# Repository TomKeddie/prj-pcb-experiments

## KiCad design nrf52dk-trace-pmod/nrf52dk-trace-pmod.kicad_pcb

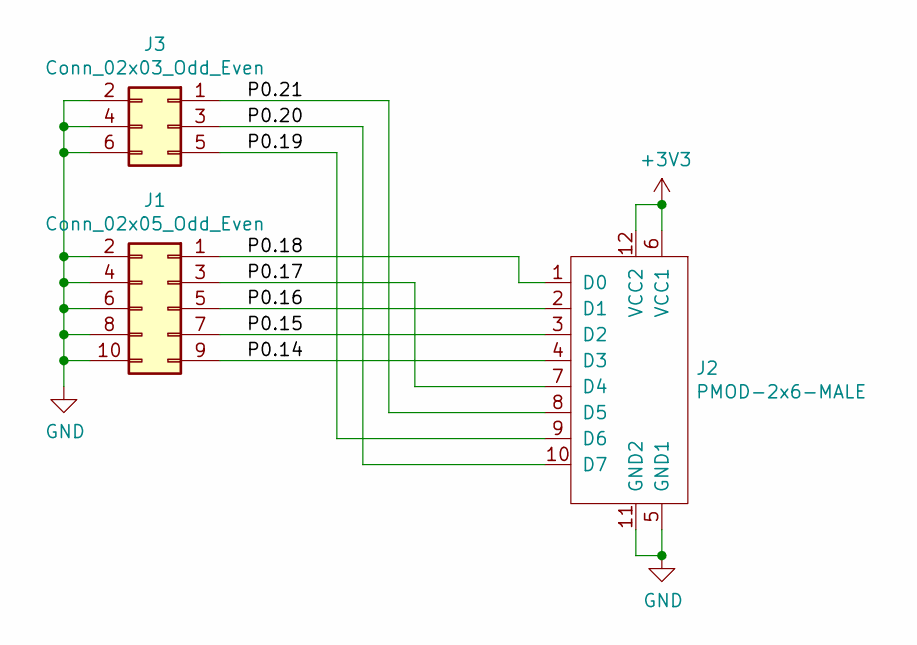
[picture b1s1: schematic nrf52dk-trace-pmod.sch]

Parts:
J1: Conn_02x05_Odd_Even; PinSocket_2x05_P2.54mm_Horizontal
J2: PMOD-2x6-MALE; PMOD_2X6_PTH_RA_PLUG
J3: Conn_02x03_Odd_Even; PinSocket_2x03_P2.54mm_Horizontal

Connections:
+3V3: J2.6 (VCC1), J2.12 (VCC2)
/P0.14: J1.9, J2.4 (D3)
/P0.15: J1.7, J2.3 (D2)
/P0.16: J1.5, J2.2 (D1)
/P0.17: J1.3, J2.7 (D4)
/P0.18: J1.1, J2.1 (D0)
/P0.19: J2.9 (D6), J3.5
/P0.20: J2.10 (D7), J3.3
/P0.21: J2.8 (D5), J3.1
GND: J1.2, J1.4, J1.6, J1.8, J1.10, J2.5 (GND1), J2.11 (GND2), J3.2, J3.4, J3.6

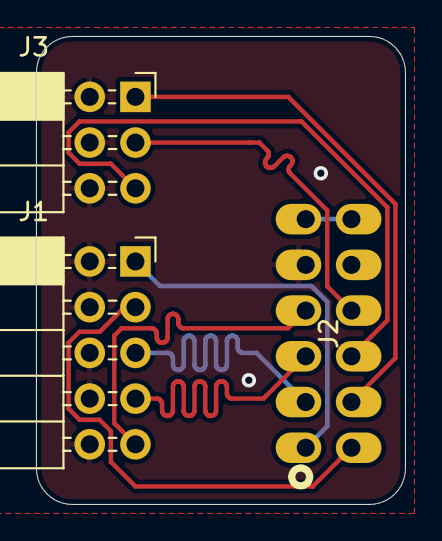
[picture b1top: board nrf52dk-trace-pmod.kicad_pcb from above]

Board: 2 copper layers, 20.5 x 26.0 mm, 3 parts (0 on the bottom side), 10 nets.

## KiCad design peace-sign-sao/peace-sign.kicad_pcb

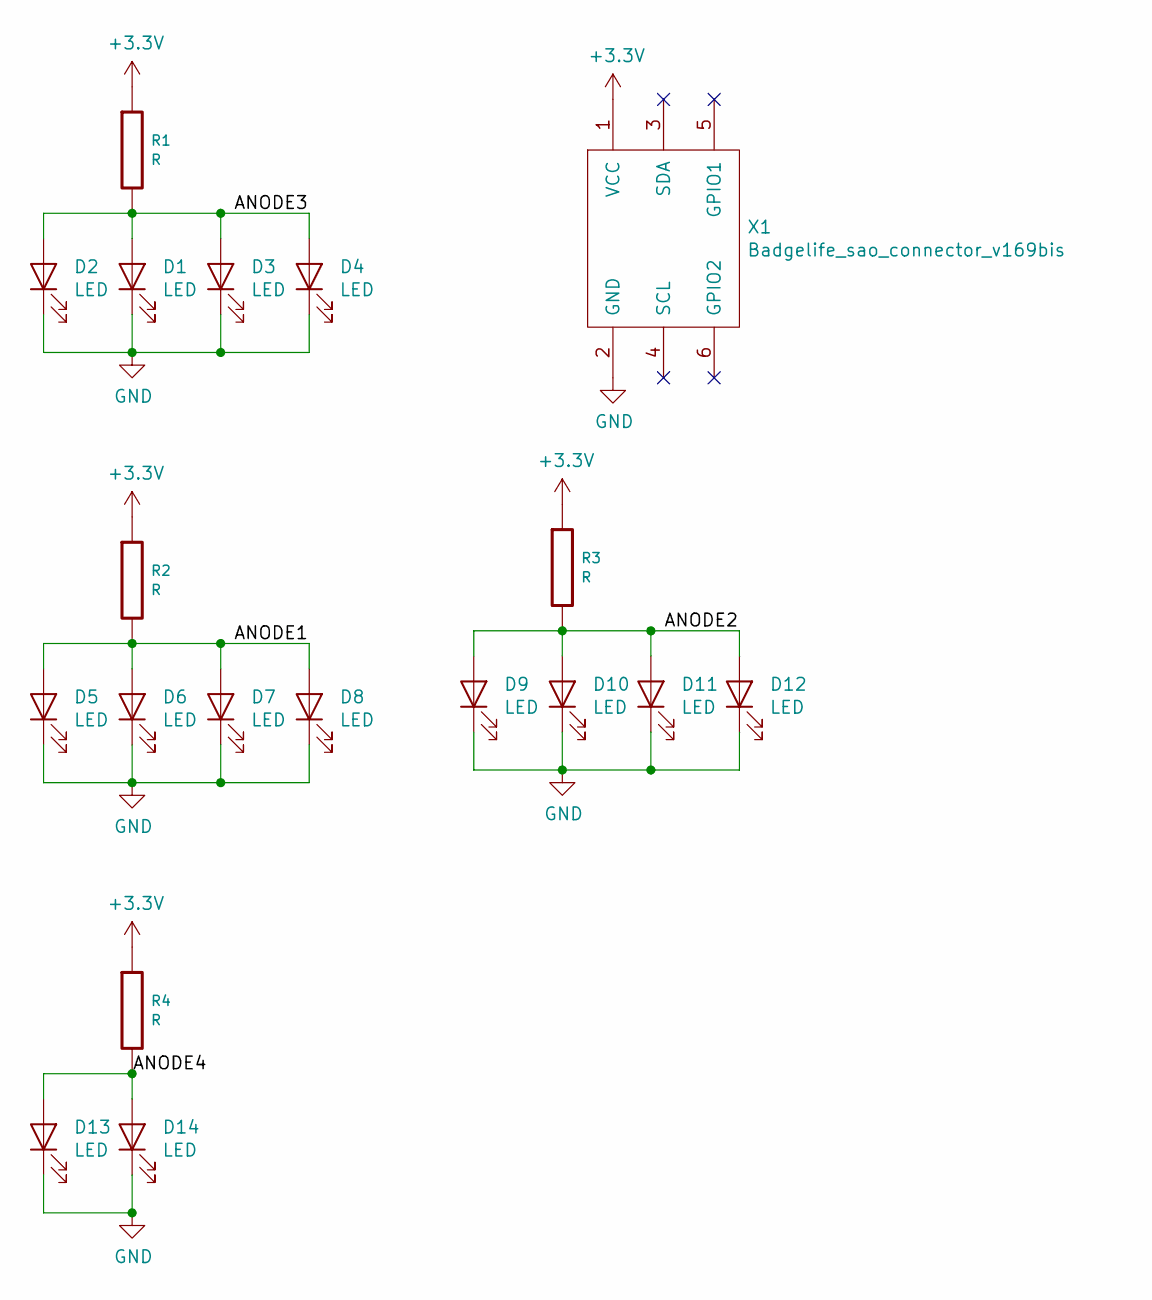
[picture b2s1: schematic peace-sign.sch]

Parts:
D1, D2, D3, D4, D5, D6, D7, D8, D9, D10, D11, D12, D13, D14: LED; ALIEXPRESS_LED_SIDE_1204
R1, R2, R3, R4: R; R_1206_3216Metric
X1: Badgelife_sao_connector_v169bis; Badgelife-SAOv169-SAO-2x3-SMD

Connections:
+3V3: R1.1, R2.1, R3.1, R4.1, X1.1 (VCC)
/ANODE1: D5.2 (A), D6.2 (A), D7.2 (A), D8.2 (A), R2.2
/ANODE2: D9.2 (A), D10.2 (A), D11.2 (A), D12.2 (A), R3.2
/ANODE3: D1.2 (A), D2.2 (A), D3.2 (A), D4.2 (A), R1.2
/ANODE4: D13.2 (A), D14.2 (A), R4.2
GND: D1.1 (K), D2.1 (K), D3.1 (K), D4.1 (K), D5.1 (K), D6.1 (K), D7.1 (K), D8.1 (K), D9.1 (K), D10.1 (K), D11.1 (K), D12.1 (K), D13.1 (K), D14.1 (K), X1.2 (GND)

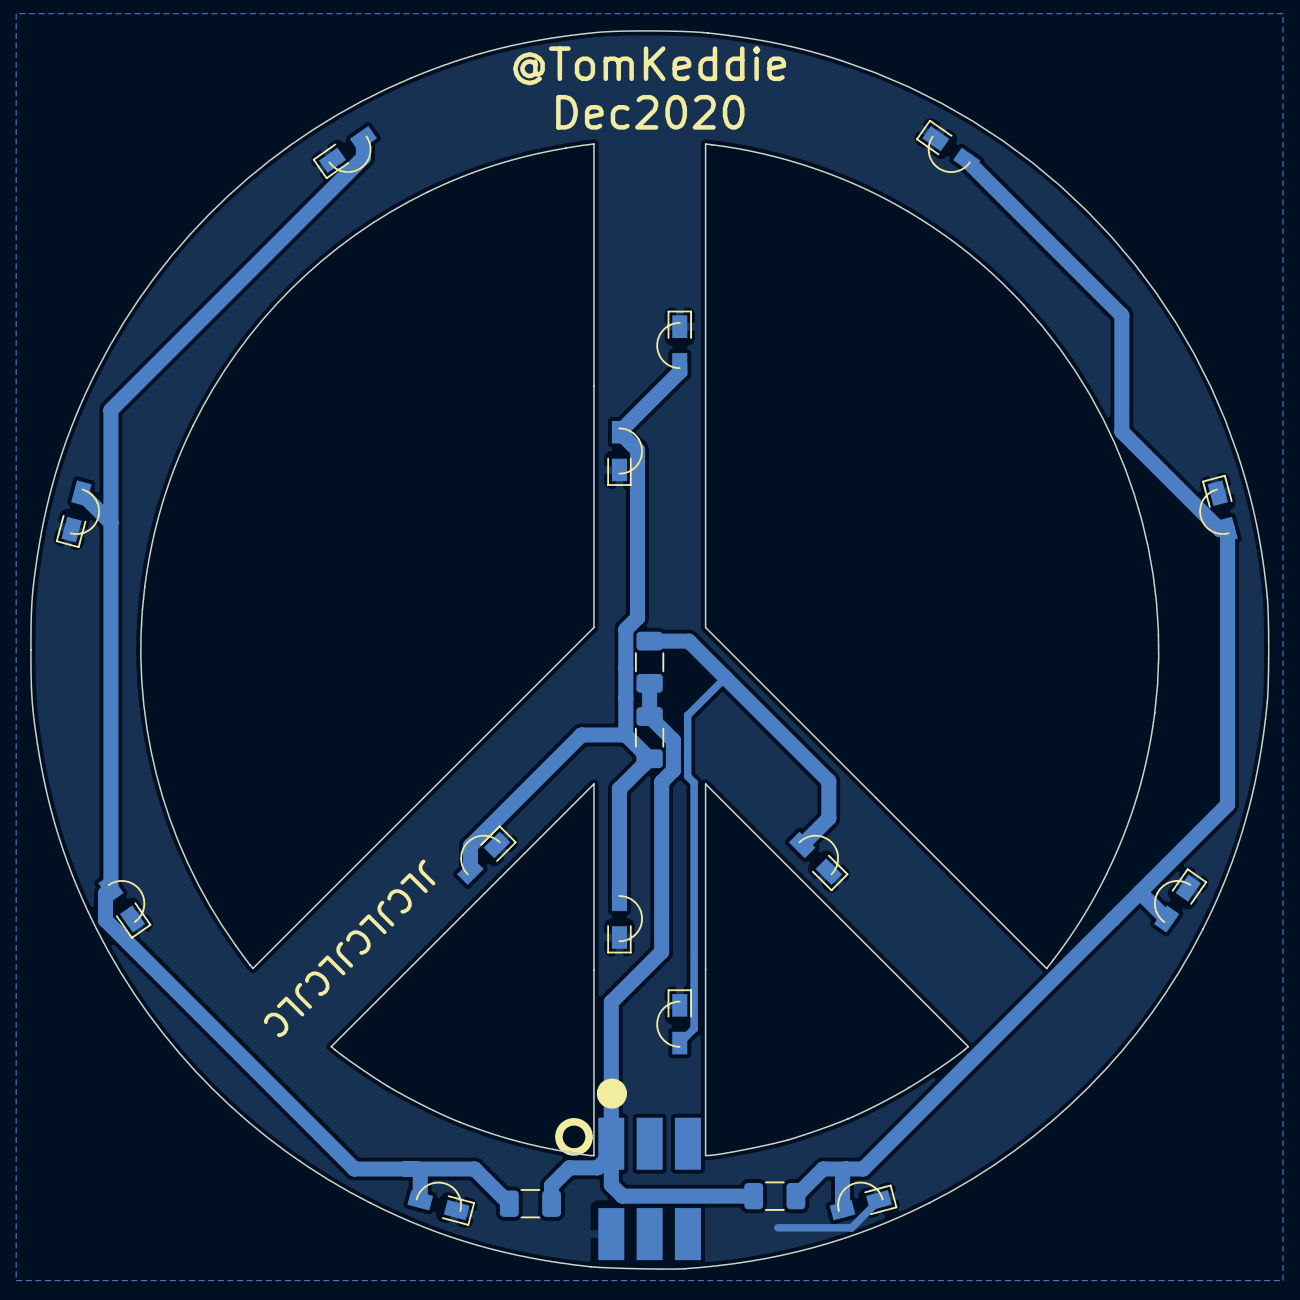
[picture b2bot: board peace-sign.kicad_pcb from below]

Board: 2 copper layers, 82.1 x 82.1 mm, 19 parts (19 on the bottom side), 6 nets.

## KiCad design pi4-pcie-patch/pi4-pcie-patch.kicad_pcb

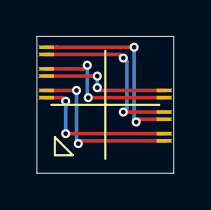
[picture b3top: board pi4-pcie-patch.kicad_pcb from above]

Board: 2 copper layers, 7.6 x 7.6 mm, 12 parts (0 on the bottom side), 6 nets.

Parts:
TP21, TP22, TP24, TP25, TP27, TP28, TP52, TP53, TP55, TP56, TP58, TP59: TestPoint; PAD_0.2_1.0MM_CAST

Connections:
/PEXRX_SSRX_N: TP28.1, TP56.1
/PEXRX_SSRX_P: TP27.1, TP55.1
/SSTX_PEXTX_N: TP25.1, TP53.1
/SSTX_PEXTX_P: TP24.1, TP52.1
/USB2D_PXECLK_N: TP22.1, TP59.1
/USB2D_PXECLK_P: TP21.1, TP58.1

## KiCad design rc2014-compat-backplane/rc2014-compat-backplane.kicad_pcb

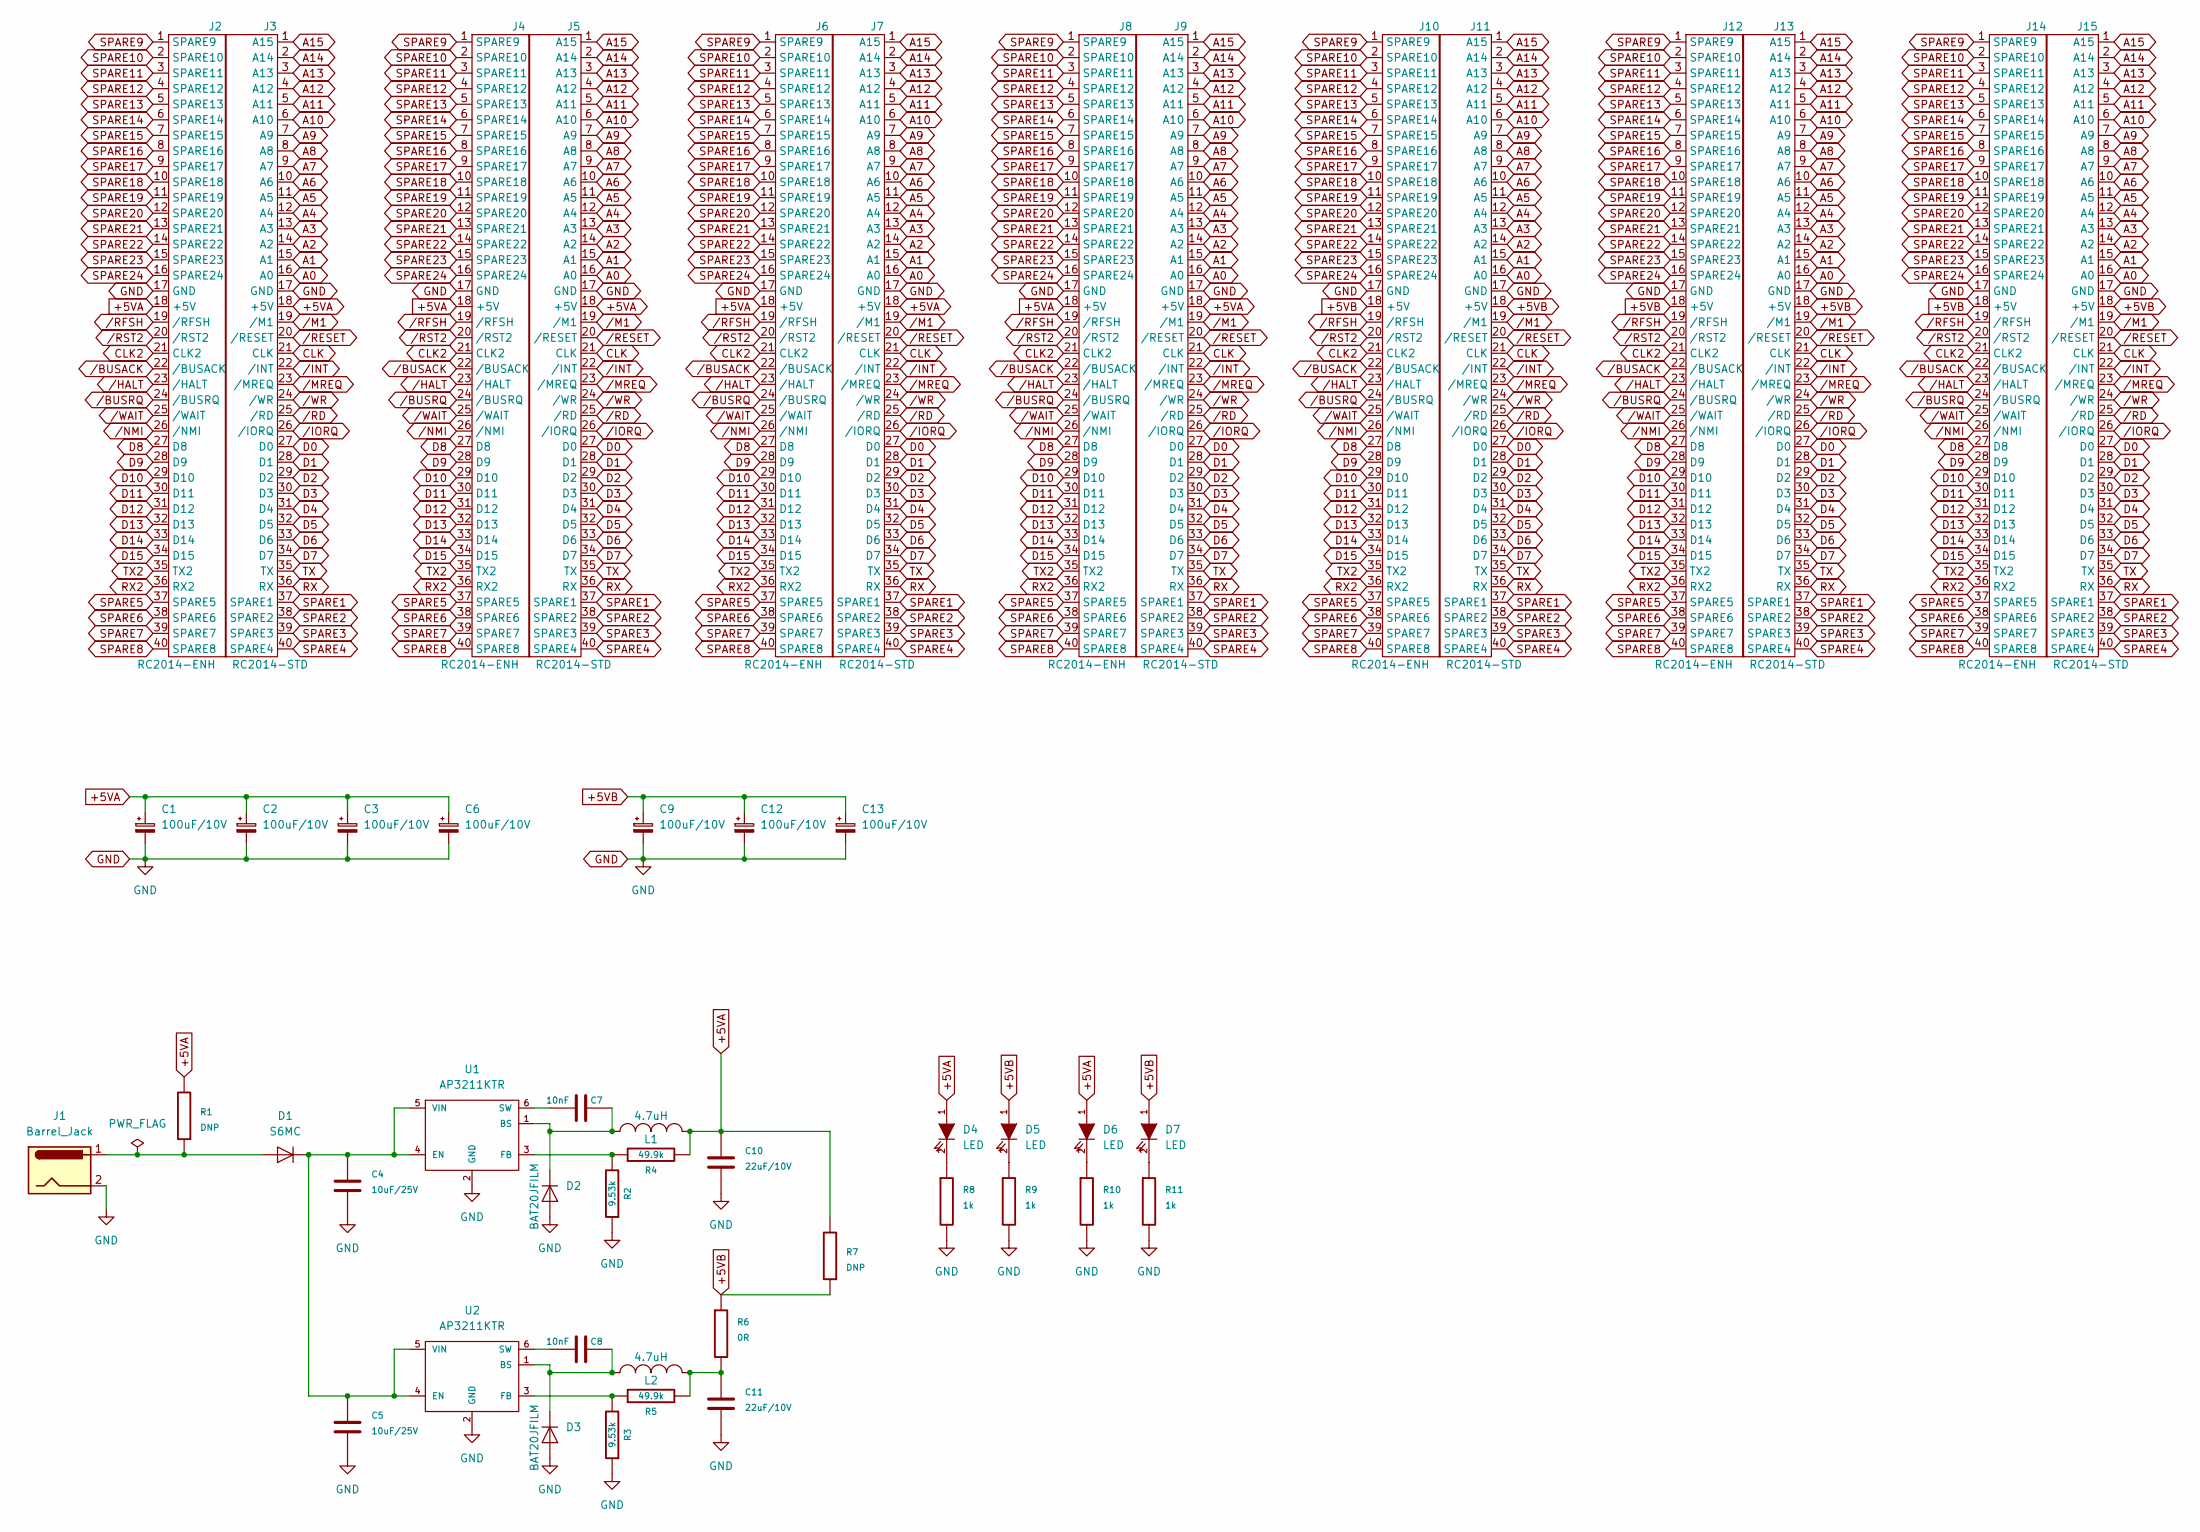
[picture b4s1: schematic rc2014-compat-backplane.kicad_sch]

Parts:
C1, C2, C3, C6, C9, C12: 100uF/10V; CP_MIXED_SMT_PTH_7343_5mm; LCSC DNP
C4, C5: 10uF/25V; C_0805_2012Metric_Pad1.15x1.40mm_HandSolder; LCSC DNP
C7, C8: 10nF; C_0805_2012Metric; LCSC DNP
C10, C11: 22uF/10V; C_0805_2012Metric_Pad1.15x1.40mm_HandSolder; LCSC DNP
C13: 100uF/10V; CP_EIA-7343-31_Kemet-D_Pad2.25x2.55mm_HandSolder; LCSC DNP
D1: S6MC; D_SMC; LCSC C382843
D2, D3: BAT20JFILM; D_SOD-323_HandSoldering
D4, D5: LED; LED_1206_3216Metric
D6, D7: LED; LED_D5.0mm
J1: Barrel_Jack; BarrelJack_CLIFF_FC681465S_SMT_Horizontal
J2, J4, J6, J8, J10, J12, J14: RC2014-ENH
J3, J5, J7, J9, J11, J13, J15: RC2014-STD
L1, L2: 4.7uH; L_Taiyo-Yuden_NR-50xx
R1, R7: DNP; R_Axial_DIN0204_L3.6mm_D1.6mm_P5.08mm_Horizontal; LCSC DNP
R2, R3: 9.53k; R_0805_2012Metric; LCSC DNP
R4, R5: 49.9k; R_0805_2012Metric; LCSC DNP
R6: 0R; R_0805_2012Metric; LCSC DNP
R8, R9: 1k; R_0805_2012Metric; LCSC DNP
R10, R11: 1k; R_Axial_DIN0204_L3.6mm_D1.6mm_P5.08mm_Horizontal; LCSC DNP
U1, U2: AP3211KTR; SOT-23-6

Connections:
+5VA: C1.1, C2.1, C3.1, C6.1, C10.1, D4.1 (A), D6.1 (A), J2.18 (+5V), J3.18 (+5V), J4.18 (+5V), J5.18 (+5V), J6.18 (+5V), J7.18 (+5V), J8.18 (+5V), J9.18 (+5V), L1.2, R1.2, R4.2, R7.2
+5VB: C9.1, C12.1, C13.1, D5.1 (A), D7.1 (A), J10.18 (+5V), J11.18 (+5V), J12.18 (+5V), J13.18 (+5V), J14.18 (+5V), J15.18 (+5V), R6.1, R7.1
A0: J3.16 (A0), J5.16 (A0), J7.16 (A0), J9.16 (A0), J11.16 (A0), J13.16 (A0), J15.16 (A0)
A1: J3.15 (A1), J5.15 (A1), J7.15 (A1), J9.15 (A1), J11.15 (A1), J13.15 (A1), J15.15 (A1)
A2: J3.14 (A2), J5.14 (A2), J7.14 (A2), J9.14 (A2), J11.14 (A2), J13.14 (A2), J15.14 (A2)
A3: J3.13 (A3), J5.13 (A3), J7.13 (A3), J9.13 (A3), J11.13 (A3), J13.13 (A3), J15.13 (A3)
A4: J3.12 (A4), J5.12 (A4), J7.12 (A4), J9.12 (A4), J11.12 (A4), J13.12 (A4), J15.12 (A4)
A5: J3.11 (A5), J5.11 (A5), J7.11 (A5), J9.11 (A5), J11.11 (A5), J13.11 (A5), J15.11 (A5)
A6: J3.10 (A6), J5.10 (A6), J7.10 (A6), J9.10 (A6), J11.10 (A6), J13.10 (A6), J15.10 (A6)
A7: J3.9 (A7), J5.9 (A7), J7.9 (A7), J9.9 (A7), J11.9 (A7), J13.9 (A7), J15.9 (A7)
A8: J3.8 (A8), J5.8 (A8), J7.8 (A8), J9.8 (A8), J11.8 (A8), J13.8 (A8), J15.8 (A8)
A9: J3.7 (A9), J5.7 (A9), J7.7 (A9), J9.7 (A9), J11.7 (A9), J13.7 (A9), J15.7 (A9)
A10: J3.6 (A10), J5.6 (A10), J7.6 (A10), J9.6 (A10), J11.6 (A10), J13.6 (A10), J15.6 (A10)
A11: J3.5 (A11), J5.5 (A11), J7.5 (A11), J9.5 (A11), J11.5 (A11), J13.5 (A11), J15.5 (A11)
A12: J3.4 (A12), J5.4 (A12), J7.4 (A12), J9.4 (A12), J11.4 (A12), J13.4 (A12), J15.4 (A12)
A13: J3.3 (A13), J5.3 (A13), J7.3 (A13), J9.3 (A13), J11.3 (A13), J13.3 (A13), J15.3 (A13)
A14: J3.2 (A14), J5.2 (A14), J7.2 (A14), J9.2 (A14), J11.2 (A14), J13.2 (A14), J15.2 (A14)
A15: J3.1 (A15), J5.1 (A15), J7.1 (A15), J9.1 (A15), J11.1 (A15), J13.1 (A15), J15.1 (A15)
CLK: J3.21 (CLK), J5.21 (CLK), J7.21 (CLK), J9.21 (CLK), J11.21 (CLK), J13.21 (CLK), J15.21 (CLK)
CLK2: J2.21 (CLK2), J4.21 (CLK2), J6.21 (CLK2), J8.21 (CLK2), J10.21 (CLK2), J12.21 (CLK2), J14.21 (CLK2)
D0: J3.27 (D0), J5.27 (D0), J7.27 (D0), J9.27 (D0), J11.27 (D0), J13.27 (D0), J15.27 (D0)
D1: J3.28 (D1), J5.28 (D1), J7.28 (D1), J9.28 (D1), J11.28 (D1), J13.28 (D1), J15.28 (D1)
D2: J3.29 (D2), J5.29 (D2), J7.29 (D2), J9.29 (D2), J11.29 (D2), J13.29 (D2), J15.29 (D2)
D3: J3.30 (D3), J5.30 (D3), J7.30 (D3), J9.30 (D3), J11.30 (D3), J13.30 (D3), J15.30 (D3)
D4: J3.31 (D4), J5.31 (D4), J7.31 (D4), J9.31 (D4), J11.31 (D4), J13.31 (D4), J15.31 (D4)
D5: J3.32 (D5), J5.32 (D5), J7.32 (D5), J9.32 (D5), J11.32 (D5), J13.32 (D5), J15.32 (D5)
D6: J3.33 (D6), J5.33 (D6), J7.33 (D6), J9.33 (D6), J11.33 (D6), J13.33 (D6), J15.33 (D6)
D7: J3.34 (D7), J5.34 (D7), J7.34 (D7), J9.34 (D7), J11.34 (D7), J13.34 (D7), J15.34 (D7)
D8: J2.27 (D8), J4.27 (D8), J6.27 (D8), J8.27 (D8), J10.27 (D8), J12.27 (D8), J14.27 (D8)
D9: J2.28 (D9), J4.28 (D9), J6.28 (D9), J8.28 (D9), J10.28 (D9), J12.28 (D9), J14.28 (D9)
D10: J2.29 (D10), J4.29 (D10), J6.29 (D10), J8.29 (D10), J10.29 (D10), J12.29 (D10), J14.29 (D10)
D11: J2.30 (D11), J4.30 (D11), J6.30 (D11), J8.30 (D11), J10.30 (D11), J12.30 (D11), J14.30 (D11)
D12: J2.31 (D12), J4.31 (D12), J6.31 (D12), J8.31 (D12), J10.31 (D12), J12.31 (D12), J14.31 (D12)
D13: J2.32 (D13), J4.32 (D13), J6.32 (D13), J8.32 (D13), J10.32 (D13), J12.32 (D13), J14.32 (D13)
D14: J2.33 (D14), J4.33 (D14), J6.33 (D14), J8.33 (D14), J10.33 (D14), J12.33 (D14), J14.33 (D14)
D15: J2.34 (D15), J4.34 (D15), J6.34 (D15), J8.34 (D15), J10.34 (D15), J12.34 (D15), J14.34 (D15)
GND: C1.2, C2.2, C3.2, C4.2, C5.2, C6.2, C9.2, C10.2, C11.2, C12.2, C13.2, D2.2 (A), D3.2 (A), J1.2, J2.17 (GND), J3.17 (GND), J4.17 (GND), J5.17 (GND), J6.17 (GND), J7.17 (GND), J8.17 (GND), J9.17 (GND), J10.17 (GND), J11.17 (GND), J12.17 (GND), J13.17 (GND), J14.17 (GND), J15.17 (GND), R2.1, R3.1, R8.2, R9.2, R10.2, R11.2, U1.2 (GND), U2.2 (GND)
unnamed: C4.1, C5.1, D1.1 (K), U1.4 (EN), U1.5 (VIN), U2.4 (EN), U2.5 (VIN)
unnamed: C7.1, U1.6 (SW)
unnamed: C7.2, D2.1 (K), L1.1, U1.1 (BS)
unnamed: C8.1, U2.6 (SW)
unnamed: C8.2, D3.1 (K), L2.1, U2.1 (BS)
unnamed: C11.1, L2.2, R5.2, R6.2
unnamed: D1.2 (A), J1.1, R1.1
unnamed: D4.2 (K), R8.1
unnamed: D5.2 (K), R9.1
unnamed: D6.2 (K), R10.1
unnamed: D7.2 (K), R11.1
unnamed: R2.2, R4.1, U1.3 (FB)
unnamed: R3.2, R5.1, U2.3 (FB)
RX: J3.36 (RX), J5.36 (RX), J7.36 (RX), J9.36 (RX), J11.36 (RX), J13.36 (RX), J15.36 (RX)
RX2: J2.36 (RX2), J4.36 (RX2), J6.36 (RX2), J8.36 (RX2), J10.36 (RX2), J12.36 (RX2), J14.36 (RX2)
SPARE1: J3.37 (SPARE1), J5.37 (SPARE1), J7.37 (SPARE1), J9.37 (SPARE1), J11.37 (SPARE1), J13.37 (SPARE1), J15.37 (SPARE1)
SPARE2: J3.38 (SPARE2), J5.38 (SPARE2), J7.38 (SPARE2), J9.38 (SPARE2), J11.38 (SPARE2), J13.38 (SPARE2), J15.38 (SPARE2)
SPARE3: J3.39 (SPARE3), J5.39 (SPARE3), J7.39 (SPARE3), J9.39 (SPARE3), J11.39 (SPARE3), J13.39 (SPARE3), J15.39 (SPARE3)
SPARE4: J3.40 (SPARE4), J5.40 (SPARE4), J7.40 (SPARE4), J9.40 (SPARE4), J11.40 (SPARE4), J13.40 (SPARE4), J15.40 (SPARE4)
SPARE5: J2.37 (SPARE5), J4.37 (SPARE5), J6.37 (SPARE5), J8.37 (SPARE5), J10.37 (SPARE5), J12.37 (SPARE5), J14.37 (SPARE5)
SPARE6: J2.38 (SPARE6), J4.38 (SPARE6), J6.38 (SPARE6), J8.38 (SPARE6), J10.38 (SPARE6), J12.38 (SPARE6), J14.38 (SPARE6)
SPARE7: J2.39 (SPARE7), J4.39 (SPARE7), J6.39 (SPARE7), J8.39 (SPARE7), J10.39 (SPARE7), J12.39 (SPARE7), J14.39 (SPARE7)
SPARE8: J2.40 (SPARE8), J4.40 (SPARE8), J6.40 (SPARE8), J8.40 (SPARE8), J10.40 (SPARE8), J12.40 (SPARE8), J14.40 (SPARE8)
SPARE9: J2.1 (SPARE9), J4.1 (SPARE9), J6.1 (SPARE9), J8.1 (SPARE9), J10.1 (SPARE9), J12.1 (SPARE9), J14.1 (SPARE9)
SPARE10: J2.2 (SPARE10), J4.2 (SPARE10), J6.2 (SPARE10), J8.2 (SPARE10), J10.2 (SPARE10), J12.2 (SPARE10), J14.2 (SPARE10)
SPARE11: J2.3 (SPARE11), J4.3 (SPARE11), J6.3 (SPARE11), J8.3 (SPARE11), J10.3 (SPARE11), J12.3 (SPARE11), J14.3 (SPARE11)
SPARE12: J2.4 (SPARE12), J4.4 (SPARE12), J6.4 (SPARE12), J8.4 (SPARE12), J10.4 (SPARE12), J12.4 (SPARE12), J14.4 (SPARE12)
SPARE13: J2.5 (SPARE13), J4.5 (SPARE13), J6.5 (SPARE13), J8.5 (SPARE13), J10.5 (SPARE13), J12.5 (SPARE13), J14.5 (SPARE13)
SPARE14: J2.6 (SPARE14), J4.6 (SPARE14), J6.6 (SPARE14), J8.6 (SPARE14), J10.6 (SPARE14), J12.6 (SPARE14), J14.6 (SPARE14)
SPARE15: J2.7 (SPARE15), J4.7 (SPARE15), J6.7 (SPARE15), J8.7 (SPARE15), J10.7 (SPARE15), J12.7 (SPARE15), J14.7 (SPARE15)
SPARE16: J2.8 (SPARE16), J4.8 (SPARE16), J6.8 (SPARE16), J8.8 (SPARE16), J10.8 (SPARE16), J12.8 (SPARE16), J14.8 (SPARE16)
SPARE17: J2.9 (SPARE17), J4.9 (SPARE17), J6.9 (SPARE17), J8.9 (SPARE17), J10.9 (SPARE17), J12.9 (SPARE17), J14.9 (SPARE17)
SPARE18: J2.10 (SPARE18), J4.10 (SPARE18), J6.10 (SPARE18), J8.10 (SPARE18), J10.10 (SPARE18), J12.10 (SPARE18), J14.10 (SPARE18)
SPARE19: J2.11 (SPARE19), J4.11 (SPARE19), J6.11 (SPARE19), J8.11 (SPARE19), J10.11 (SPARE19), J12.11 (SPARE19), J14.11 (SPARE19)
SPARE20: J2.12 (SPARE20), J4.12 (SPARE20), J6.12 (SPARE20), J8.12 (SPARE20), J10.12 (SPARE20), J12.12 (SPARE20), J14.12 (SPARE20)
SPARE21: J2.13 (SPARE21), J4.13 (SPARE21), J6.13 (SPARE21), J8.13 (SPARE21), J10.13 (SPARE21), J12.13 (SPARE21), J14.13 (SPARE21)
SPARE22: J2.14 (SPARE22), J4.14 (SPARE22), J6.14 (SPARE22), J8.14 (SPARE22), J10.14 (SPARE22), J12.14 (SPARE22), J14.14 (SPARE22)
SPARE23: J2.15 (SPARE23), J4.15 (SPARE23), J6.15 (SPARE23), J8.15 (SPARE23), J10.15 (SPARE23), J12.15 (SPARE23), J14.15 (SPARE23)
SPARE24: J2.16 (SPARE24), J4.16 (SPARE24), J6.16 (SPARE24), J8.16 (SPARE24), J10.16 (SPARE24), J12.16 (SPARE24), J14.16 (SPARE24)
TX: J3.35 (TX), J5.35 (TX), J7.35 (TX), J9.35 (TX), J11.35 (TX), J13.35 (TX), J15.35 (TX)
TX2: J2.35 (TX2), J4.35 (TX2), J6.35 (TX2), J8.35 (TX2), J10.35 (TX2), J12.35 (TX2), J14.35 (TX2)
/BUSACK: J2.22 (/BUSACK), J4.22 (/BUSACK), J6.22 (/BUSACK), J8.22 (/BUSACK), J10.22 (/BUSACK), J12.22 (/BUSACK), J14.22 (/BUSACK)
/BUSRQ: J2.24 (/BUSRQ), J4.24 (/BUSRQ), J6.24 (/BUSRQ), J8.24 (/BUSRQ), J10.24 (/BUSRQ), J12.24 (/BUSRQ), J14.24 (/BUSRQ)
/HALT: J2.23 (/HALT), J4.23 (/HALT), J6.23 (/HALT), J8.23 (/HALT), J10.23 (/HALT), J12.23 (/HALT), J14.23 (/HALT)
/INT: J3.22 (/INT), J5.22 (/INT), J7.22 (/INT), J9.22 (/INT), J11.22 (/INT), J13.22 (/INT), J15.22 (/INT)
/IORQ: J3.26 (/IORQ), J5.26 (/IORQ), J7.26 (/IORQ), J9.26 (/IORQ), J11.26 (/IORQ), J13.26 (/IORQ), J15.26 (/IORQ)
/M1: J3.19 (/M1), J5.19 (/M1), J7.19 (/M1), J9.19 (/M1), J11.19 (/M1), J13.19 (/M1), J15.19 (/M1)
/MREQ: J3.23 (/MREQ), J5.23 (/MREQ), J7.23 (/MREQ), J9.23 (/MREQ), J11.23 (/MREQ), J13.23 (/MREQ), J15.23 (/MREQ)
/NMI: J2.26 (/NMI), J4.26 (/NMI), J6.26 (/NMI), J8.26 (/NMI), J10.26 (/NMI), J12.26 (/NMI), J14.26 (/NMI)
/RD: J3.25 (/RD), J5.25 (/RD), J7.25 (/RD), J9.25 (/RD), J11.25 (/RD), J13.25 (/RD), J15.25 (/RD)
/RESET: J3.20 (/RESET), J5.20 (/RESET), J7.20 (/RESET), J9.20 (/RESET), J11.20 (/RESET), J13.20 (/RESET), J15.20 (/RESET)
/RFSH: J2.19 (/RFSH), J4.19 (/RFSH), J6.19 (/RFSH), J8.19 (/RFSH), J10.19 (/RFSH), J12.19 (/RFSH), J14.19 (/RFSH)
/RST2: J2.20 (/RST2), J4.20 (/RST2), J6.20 (/RST2), J8.20 (/RST2), J10.20 (/RST2), J12.20 (/RST2), J14.20 (/RST2)
/WAIT: J2.25 (/WAIT), J4.25 (/WAIT), J6.25 (/WAIT), J8.25 (/WAIT), J10.25 (/WAIT), J12.25 (/WAIT), J14.25 (/WAIT)
/WR: J3.24 (/WR), J5.24 (/WR), J7.24 (/WR), J9.24 (/WR), J11.24 (/WR), J13.24 (/WR), J15.24 (/WR)

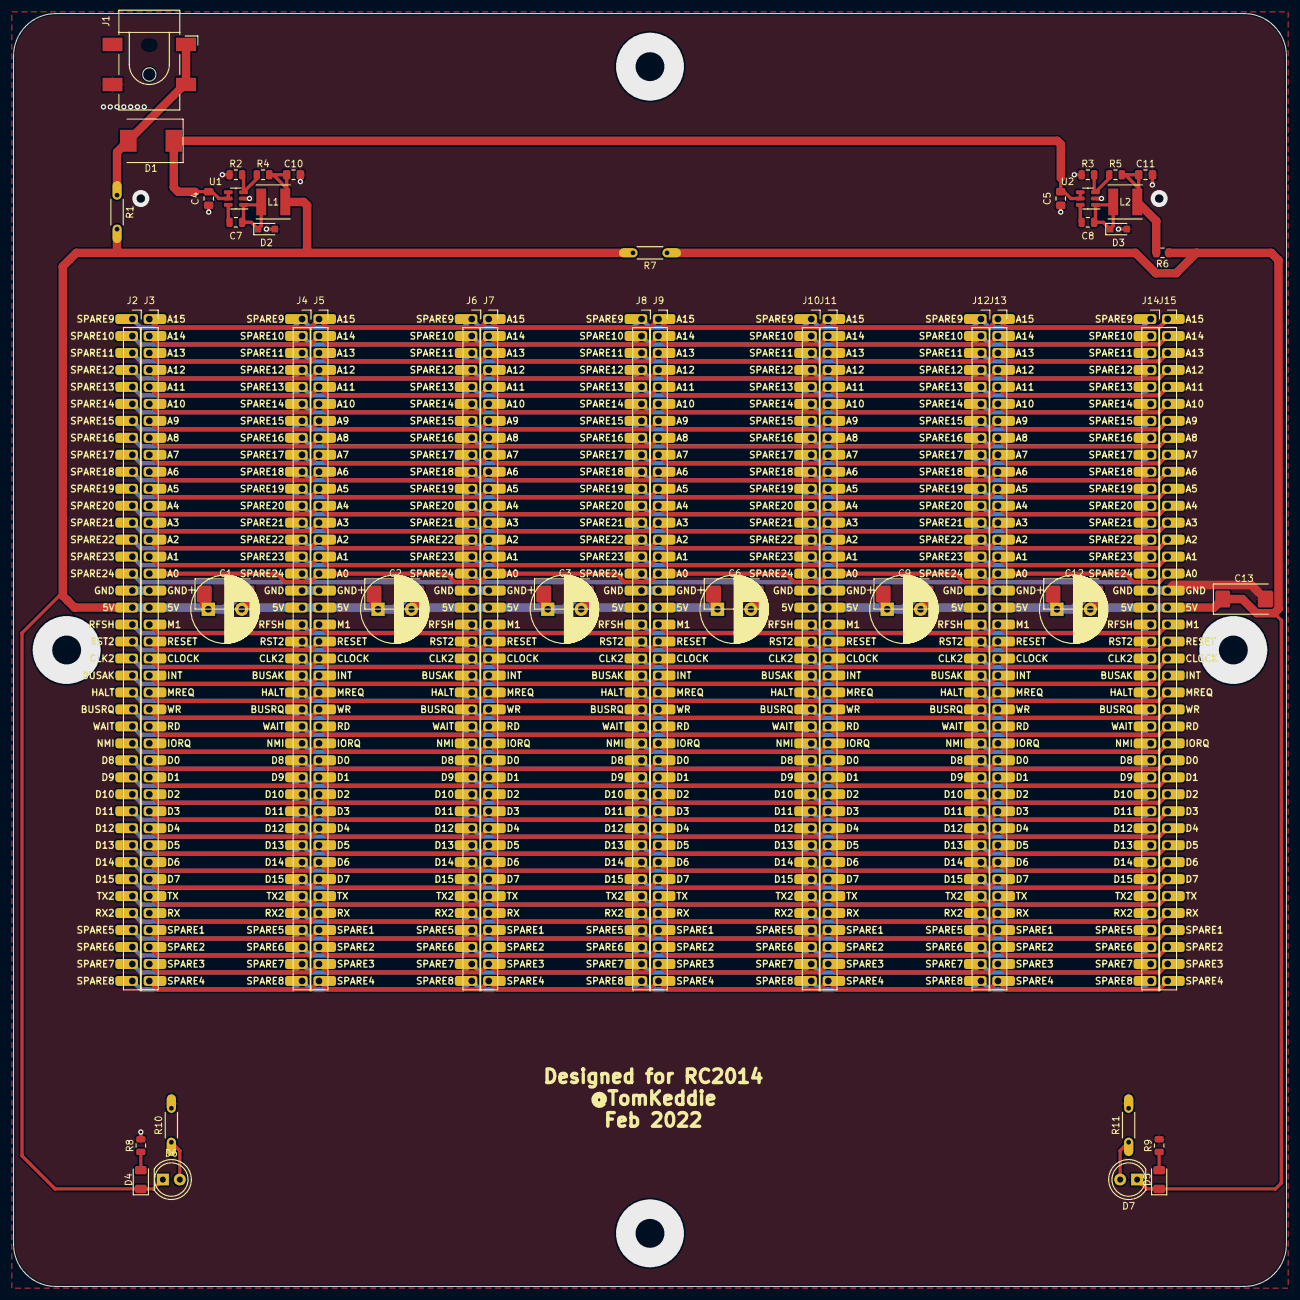
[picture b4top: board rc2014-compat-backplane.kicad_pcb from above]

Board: 2 copper layers, 190.5 x 190.5 mm, 50 parts (0 on the bottom side), 92 nets.

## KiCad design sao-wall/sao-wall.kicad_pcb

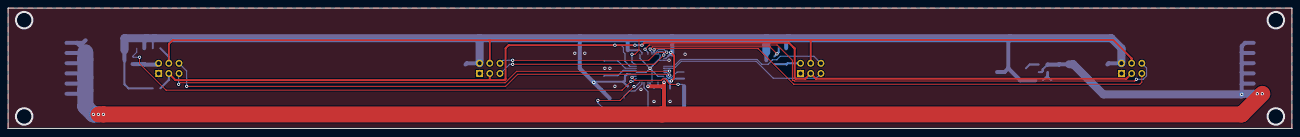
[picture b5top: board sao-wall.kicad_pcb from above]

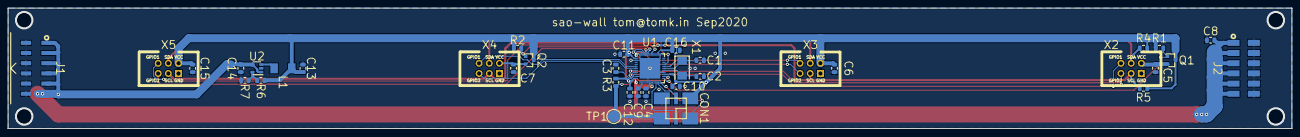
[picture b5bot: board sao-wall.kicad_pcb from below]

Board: 2 copper layers, 320.0 x 30.0 mm, 37 parts (33 on the bottom side), 27 nets.

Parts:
C1, C2: 18pF; C_0805_2012Metric
C3, C9, C10, C11, C12, C16: 0.1uF/6.3V; C_0805_2012Metric
C4: 1uF/6.3V; C_0805_2012Metric
C5, C6, C7, C8, C13, C15: 10uF/6.3V; C_0805_2012Metric
C14: 10uF/10V; C_0805_2012Metric
CON1: AVR-ISP-6; PinSocket_2x03_P2.54mm_Vertical_SMD_SAO
J1: PMOD-2x6-MALE; 2X6_SMD_RA_PLUG
J2: PMOD-2x6-FEMALE; 2X6_SMD_RA_SOCKET
L1: 2.2uH/4.5A; L_MWSA0518S
Q1, Q2: AO3401A; SOT-23
R1, R2, R3, R4, R5: 10k; R_0805_2012Metric
R6: 450k; R_0805_2012Metric
R7: 100k; R_0805_2012Metric
TP1: TestPoint; TestPoint_Pad_D3.0mm
U1: ATmega32U4-MU; QFN-44-1EP_7x7mm_P0.5mm_EP5.15x5.15mm
U2: TLV62569DBVR; SOT-23-5
X1: 16MHz; Crystal_SMD_5032-2Pin_5.0x3.2mm
X2: A; Badgelife-SAOv169-SAO-2x3
X3: B; Badgelife-SAOv169-SAO-2x3
X4: C; Badgelife-SAOv169-SAO-2x3
X5: D; Badgelife-SAOv169-SAO-2x3

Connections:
+3V3: C6.1, C10.1, C11.1, C12.1, C13.1, C15.1, C16.1, CON1.2, L1.2, Q1.3, Q2.3, R1.1, R2.1, R3.1, R4.1, R5.1, R6.1, U1.14, U1.24, U1.34, U1.44, X3.1, X5.1
+5V: C8.1, C9.1, C14.2, J1.1, J1.2, J1.3, J1.4, J1.5, J1.6, J2.1, J2.2, J2.3, J2.4, J2.5, J2.6, U1.2, U1.7, U2.1, U2.4
/!RESET: CON1.5, R3.2, TP1.1, U1.13
/AREF: C3.2, U1.42
/A_GPIO1: U1.41, X2.5
/A_GPIO2: U1.40, X2.6
/A_PWM: Q1.1, R1.2, U1.12
/A_VCC: C5.1, Q1.2, X2.1
/B_GPIO1: U1.31, X3.5
/B_GPIO2: U1.32, X3.6
/C_GPIO1: U1.38, X4.5
/C_GPIO2: U1.39, X4.6
/C_PWM: Q2.1, R2.2, U1.29
/C_VCC: C7.1, Q2.2, X4.1
/D_GPIO1: U1.27, X5.5
/D_GPIO2: U1.30, X5.6
/FB: R6.2, R7.1, U2.5
/MISO: CON1.1, U1.11
/MOSI: CON1.4, U1.10
/SCK: CON1.3, U1.9
/SCL: R5.2, U1.18, X2.4, X3.4, X4.4, X5.4
/SDA: R4.2, U1.19, X2.3, X3.3, X4.3, X5.3
/SW: L1.1, U2.3
/UCAP: C4.1, U1.6
/XTAL1: C1.1, U1.17, X1.1
/XTAL2: C2.1, U1.16, X1.2
GND: C1.2, C2.2, C3.1, C4.2, C5.2, C6.2, C7.2, C8.2, C9.2, C10.2, C11.2, C12.2, C13.2, C14.1, C15.2, C16.2, CON1.6, J1.7, J1.8, J1.9, J1.10, J1.11, J1.12, J2.7, J2.8, J2.9, J2.10, J2.11, J2.12, R7.2, U1.5, U1.15, U1.23, U1.33, U1.35, U1.43, U1.45, U2.2, X2.2, X3.2, X4.2, X5.2
